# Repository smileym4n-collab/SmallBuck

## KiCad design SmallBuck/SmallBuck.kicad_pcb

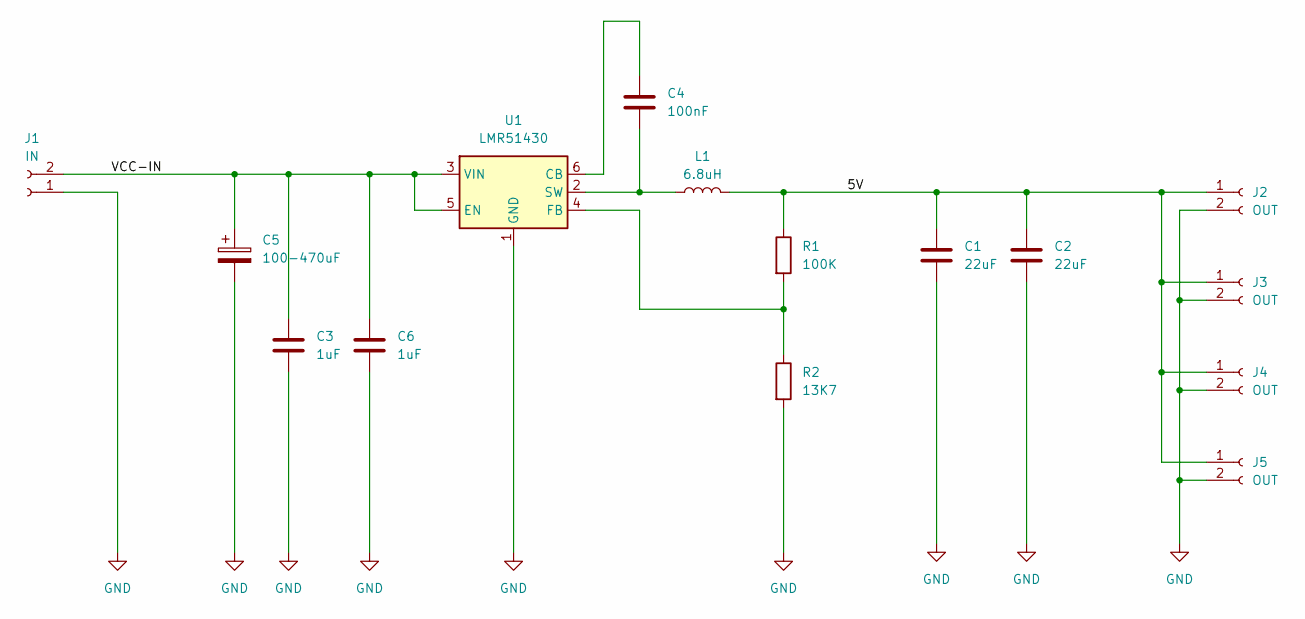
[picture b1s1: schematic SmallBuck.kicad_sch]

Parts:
C1, C2: 22uF; C_1206_3216Metric_Pad1.33x1.80mm_HandSolder
C3, C6: 1uF; C_1206_3216Metric_Pad1.33x1.80mm_HandSolder
C4: 100nF; C_1206_3216Metric_Pad1.33x1.80mm_HandSolder
C5: 100-470uF; CP_Radial_D8.0mm_P3.50mm
J1: IN; JST_XH_B2B-XH-A_1x02_P2.50mm_Vertical
J2, J3, J4, J5: OUT; JST_XH_B2B-XH-A_1x02_P2.50mm_Vertical
L1: 6.8uH; SRP6030WA-6R8M
R1: 100K; R_0805_2012Metric_Pad1.20x1.40mm_HandSolder
R2: 13K7; R_0805_2012Metric_Pad1.20x1.40mm_HandSolder
U1: LMR51430; SOT-23-6_Handsoldering

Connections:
/5V: C1.1, C2.1, J2.1, J3.1, J4.1, J5.1, L1.2, R1.1; also elsewhere on the board
/VCC-IN: C3.1, C5.1, C6.1, J1.2, U1.3 (VIN), U1.5 (EN)
GND: C1.2, C2.2, C3.2, C5.2, C6.2, J1.1, J2.2, J3.2, J4.2, J5.2, R2.2, U1.1 (GND); also elsewhere on the board
unnamed: C4.1, U1.6 (CB)
unnamed: R1.2, R2.1, U1.4 (FB)
unnamed: C4.2, L1.1, U1.2 (SW)

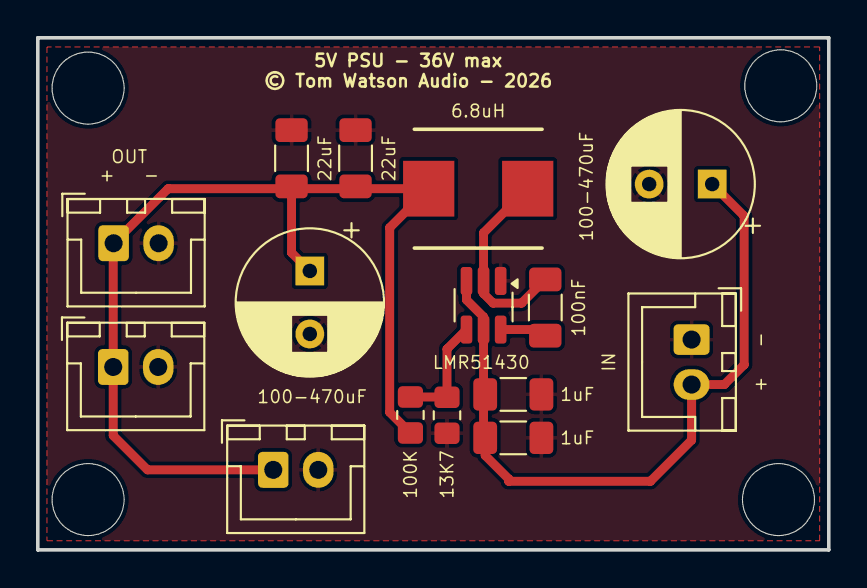
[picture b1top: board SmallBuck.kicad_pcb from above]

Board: 2 copper layers, 43.9 x 28.4 mm, 19 parts (0 on the bottom side), 6 nets.

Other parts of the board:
C7: 100-470uF; CP_Radial_D8.0mm_P3.50mm
H1, H2, H3, H4: MountingHole; MountingHole_4mm

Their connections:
/5V: C7.1; also elsewhere on the board
GND: C7.2; also elsewhere on the board

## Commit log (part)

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2026-06-04 design complete

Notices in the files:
SmallBuck/SmallBuck.kicad_pcb:
© Tom Watson Audio - 2026
